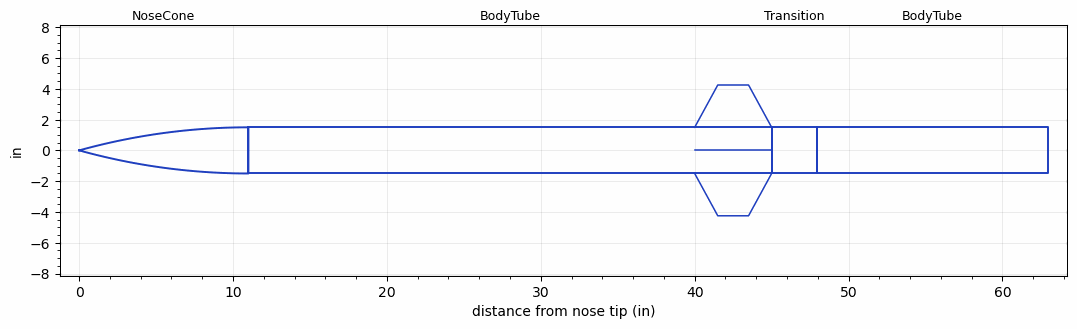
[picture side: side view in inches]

<RASAeroDocument>
 <FileVersion>2</FileVersion>
 <RocketDesign>
  <NoseCone>
   <Length>11</Length>
   <Diameter>3</Diameter>
   <Shape>Tangent Ogive</Shape>
   <Location>0</Location>
  </NoseCone>
  <BodyTube>
   <Length>33.9999</Length>
   <Diameter>3</Diameter>
   <Location>11</Location>
   <Fin>
    <Count>4</Count>
    <Chord>5</Chord>
    <Span>2.75</Span>
    <SweepDistance>1.5</SweepDistance>
    <TipChord>2</TipChord>
    <Thickness>0.25</Thickness>
    <Location>5</Location>
    <AirfoilSection>Rounded</AirfoilSection>
   </Fin>
  </BodyTube>
  <Transition>
   <Length>2.9528</Length>
   <Diameter>3</Diameter>
   <RearDiameter>3</RearDiameter>
   <Location>44.9999</Location>
  </Transition>
  <BodyTube>
   <Length>15</Length>
   <Diameter>3</Diameter>
   <Location>47.9527</Location>
  </BodyTube>
  <Surface>Rough Camouflage Paint</Surface>
  <CD>0</CD>
  <ModifiedBarrowman>False</ModifiedBarrowman>
  <Turbulence>False</Turbulence>
  <UseBooster1>False</UseBooster1>
  <UseBooster2>False</UseBooster2>
 </RocketDesign>
 <LaunchSite>
  <Altitude>5000.0002</Altitude>
  <Pressure>24.8977</Pressure>
  <RodAngle>0</RodAngle>
  <RodLength>3.2808</RodLength>
  <Temperature>41.1692</Temperature>
  <WindSpeed>4.4739</WindSpeed>
 </LaunchSite>
 <Recovery>
  <Altitude1>0</Altitude1>
  <Altitude2>0</Altitude2>
  <DeviceType1>None</DeviceType1>
  <DeviceType2>None</DeviceType2>
  <Event1>False</Event1>
  <Event2>False</Event2>
  <Size1>0</Size1>
  <Size2>0</Size2>
  <EventType1>None</EventType1>
  <EventType2>None</EventType2>
  <CD1>0</CD1>
  <CD2>0</CD2>
 </Recovery>
 <SimulationList>
  <Simulation>
   <SustainerEngine>G74W  (AT)</SustainerEngine>
   <SustainerLaunchWt>1.6055</SustainerLaunchWt>
   <SustainerCG>30.505</SustainerCG>
   <SustainerIgnitionDelay>0</SustainerIgnitionDelay>
   <Booster1SeparationDelay>0</Booster1SeparationDelay>
   <Booster1IgnitionDelay>0</Booster1IgnitionDelay>
   <IncludeBooster1>False</IncludeBooster1>
   <Booster2Delay>0</Booster2Delay>
   <IncludeBooster2>False</IncludeBooster2>
  </Simulation>
  <Simulation>
   <SustainerLaunchWt>2.1412</SustainerLaunchWt>
   <SustainerCG>33.0983</SustainerCG>
   <SustainerIgnitionDelay>0</SustainerIgnitionDelay>
   <Booster1SeparationDelay>0</Booster1SeparationDelay>
   <Booster1IgnitionDelay>0</Booster1IgnitionDelay>
   <IncludeBooster1>False</IncludeBooster1>
   <Booster2Delay>0</Booster2Delay>
   <IncludeBooster2>False</IncludeBooster2>
  </Simulation>
  <Simulation>
   <SustainerLaunchWt>1.4137</SustainerLaunchWt>
   <SustainerCG>28.7796</SustainerCG>
   <SustainerIgnitionDelay>0</SustainerIgnitionDelay>
   <Booster1SeparationDelay>0</Booster1SeparationDelay>
   <Booster1IgnitionDelay>0</Booster1IgnitionDelay>
   <IncludeBooster1>False</IncludeBooster1>
   <Booster2Delay>0</Booster2Delay>
   <IncludeBooster2>False</IncludeBooster2>
  </Simulation>
 </SimulationList>
</RASAeroDocument>
